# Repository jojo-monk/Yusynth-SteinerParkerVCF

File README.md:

# Yusynth-SteinerParkerVCF
Adaptation du Yusynth [SteinerParkerVCF](http://yusynth.net/Modular/index_en.html) au format Eurorack
Testé et Fonctionnel

J'ai fait une petite erreur sur la sérigraphie du bouton Mode qui se trouvait du mauvais côté du bouton, mais c'est corrigé dans le fichier kicad.
J'ai ajouté un trimmer 100k pour pouvoir régler la résonance.

I made a small mistake on the screen printing of the Mode button which was on the wrong side of the button, but it is corrected in the kicad file.
I added a 100k trimmer to be able to adjust the resonance.

Remplacement de la resistance R19 de 3.9K par un trimpot 100K, (souder la 3eme patte sur la patte centrale)
Replacement of the 3.9K resistor R19 with a 100K trimpot, (solder the 3rd pin on the central pin).

[Build document](https://htmlpreview.github.io/?https://github.com/jojo-monk/Yusynth-SteinerParkerVCF/blob/main/ibom.html)

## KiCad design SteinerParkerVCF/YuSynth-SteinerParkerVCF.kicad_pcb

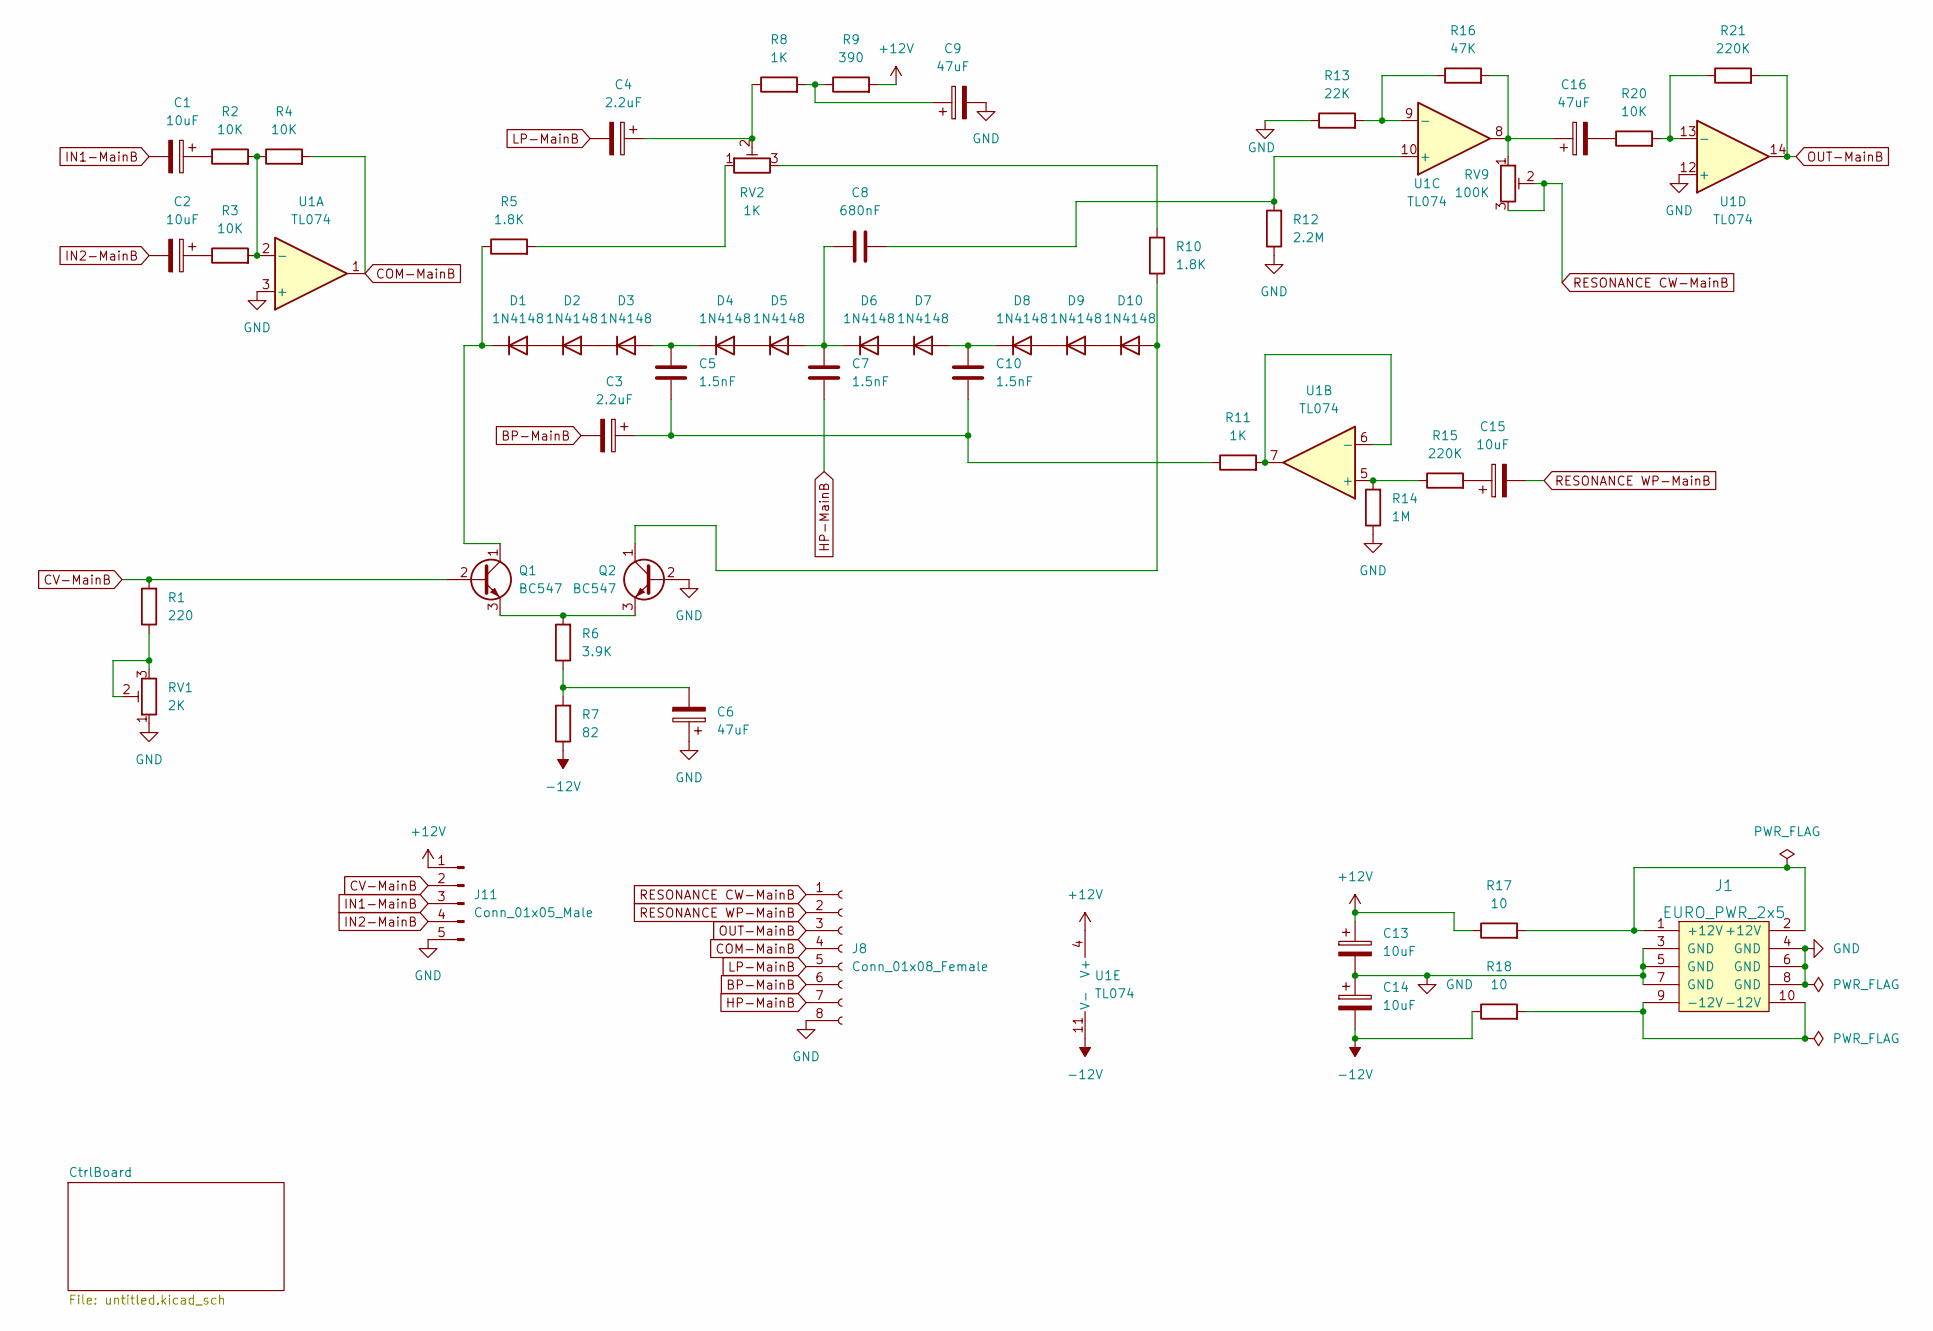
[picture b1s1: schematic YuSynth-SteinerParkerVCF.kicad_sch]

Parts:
C1, C2, C13, C14, C15: 10uF; CP_Radial_D5.0mm_P2.00mm
C3, C4: 2.2uF; CP_Radial_D5.0mm_P2.00mm
C5, C7, C10: 1.5nF; C_Rect_L7.0mm_W3.5mm_P5.00mm
C6, C9, C16: 47uF; CP_Radial_D5.0mm_P2.00mm
C8: 680nF; C_Rect_L7.0mm_W3.5mm_P5.00mm
D1, D2, D3, D4, D5, D6, D7, D8, D9, D10: 1N4148; D_DO-35_SOD27_P7.62mm_Horizontal
J1: EURO_PWR_2x5; Eurorack_power_header
J8: Conn_01x08_Female; PinHeader_1x08_P2.54mm_Vertical
J11: Conn_01x05_Male; PinHeader_1x05_P2.54mm_Vertical
Q1, Q2: BC547; TO-92_HandSolder
R1: 220; R_Axial_DIN0207_L6.3mm_D2.5mm_P5.08mm_Vertical
R2, R3, R4, R20: 10K; R_Axial_DIN0207_L6.3mm_D2.5mm_P5.08mm_Vertical
R5, R10: 1.8K; R_Axial_DIN0207_L6.3mm_D2.5mm_P5.08mm_Vertical
R6: 3.9K; R_Axial_DIN0207_L6.3mm_D2.5mm_P5.08mm_Vertical
R7: 82; R_Axial_DIN0207_L6.3mm_D2.5mm_P5.08mm_Vertical
R8, R11: 1K; R_Axial_DIN0207_L6.3mm_D2.5mm_P5.08mm_Vertical
R9: 390; R_Axial_DIN0207_L6.3mm_D2.5mm_P5.08mm_Vertical
R12: 2.2M; R_Axial_DIN0207_L6.3mm_D2.5mm_P5.08mm_Vertical
R13: 22K; R_Axial_DIN0207_L6.3mm_D2.5mm_P5.08mm_Vertical
R14: 1M; R_Axial_DIN0207_L6.3mm_D2.5mm_P5.08mm_Vertical
R15, R21: 220K; R_Axial_DIN0207_L6.3mm_D2.5mm_P5.08mm_Vertical
R16: 47K; R_Axial_DIN0207_L6.3mm_D2.5mm_P5.08mm_Vertical
R17, R18: 10; R_Axial_DIN0207_L6.3mm_D2.5mm_P5.08mm_Vertical
RV1: 2K; Potentiometer_Bourns_3266Y_Vertical
RV2: 1K; Potentiometer_Bourns_3266Y_Vertical
RV9: 100K; Potentiometer_Bourns_3266Y_Vertical
U1: TL074; DIP-14_W7.62mm_LongPads

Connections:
+12V: C13.1, J11.1, R9.2, R17.1, U1.4 (V+); also elsewhere on the board
-12V: C14.2, R7.1, R18.1, U1.11 (V-)
BP-MainB: C3.2, J8.6
COM-MainB: J8.4, R4.2, U1.1
CV-MainB: J11.2, Q1.2 (B), R1.2
GND: C6.1, C9.2, C13.2, C14.1, J1.3 (GND), J1.4 (GND), J1.5 (GND), J1.6 (GND), J1.7 (GND), J1.8 (GND), J8.8, J11.5, Q2.2 (B), R12.1, R13.1, R14.1, RV1.1, U1.3 (+), U1.12 (+); also elsewhere on the board
HP-MainB: C7.2, J8.7
IN1-MainB: C1.2, J11.3
IN2-MainB: C2.2, J11.4
LP-MainB: C4.2, J8.5
unnamed: C1.1, R2.1
unnamed: C2.1, R3.1
unnamed: C4.1, R8.1, RV2.2
unnamed: C5.1, D3.2 (A), D4.1 (K)
unnamed: C6.2, R6.1, R7.2
unnamed: C7.1, C8.1, D5.2 (A), D6.1 (K)
unnamed: C8.2, R12.2, U1.10 (+)
unnamed: C9.1, R8.2, R9.1
unnamed: C10.1, D7.2 (A), D8.1 (K)
unnamed: C3.1, C5.2, C10.2, R11.1
unnamed: C15.1, R15.2
unnamed: C16.1, R16.2, RV9.1, U1.8
unnamed: C16.2, R20.1
unnamed: D1.1 (K), Q1.1 (C), R5.1
unnamed: D1.2 (A), D2.1 (K)
unnamed: D2.2 (A), D3.1 (K)
unnamed: D4.2 (A), D5.1 (K)
unnamed: D6.2 (A), D7.1 (K)
unnamed: D8.2 (A), D9.1 (K)
unnamed: D9.2 (A), D10.1 (K)
unnamed 37: D10.2 (A), Q2.1 (C), R10.1; also elsewhere on the board
unnamed: J1.1 (+12V), J1.2 (+12V), R17.2
unnamed: J1.9 (-12V), J1.10 (-12V), R18.2
unnamed 46: Q1.3 (E), Q2.3 (E), R6.2; also elsewhere on the board
unnamed: R1.1, RV1.2, RV1.3
unnamed: R2.2, R3.2, R4.1, U1.2 (-)
unnamed: R5.2, RV2.1
unnamed: R10.2, RV2.3
unnamed: R11.2, U1.6 (-), U1.7
unnamed: R13.2, R16.1, U1.9 (-)
unnamed: R14.2, R15.1, U1.5 (+)
unnamed: R20.2, R21.1, U1.13 (-)
OUT-MainB: J8.3, R21.2, U1.14
RESONANCE CW-MainB: J8.1, RV9.2, RV9.3
RESONANCE WP-MainB: C15.2, J8.2

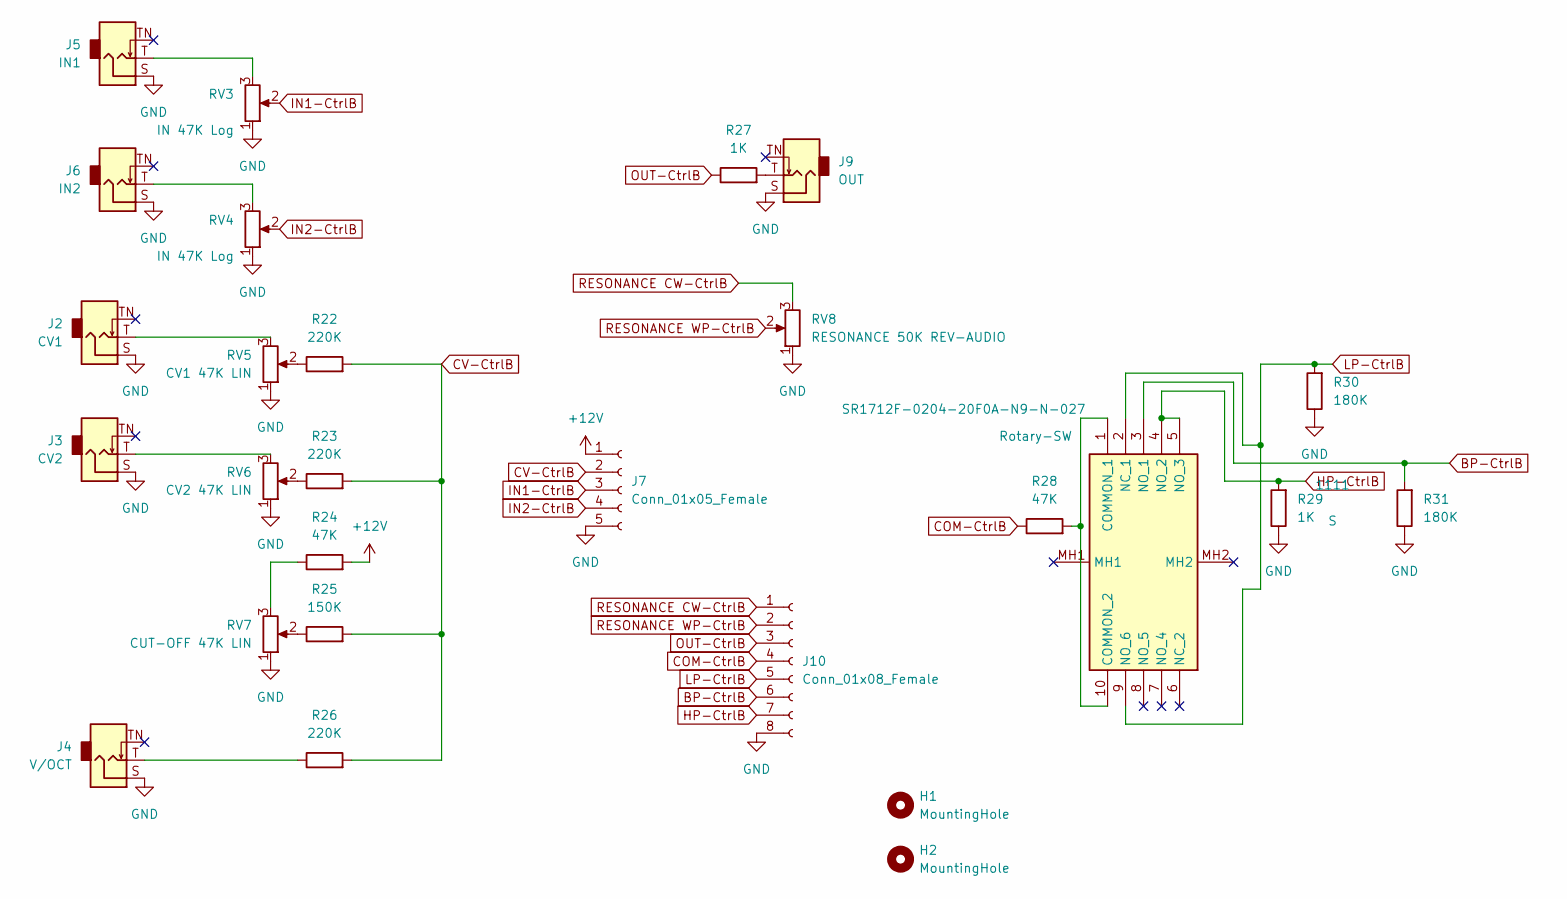
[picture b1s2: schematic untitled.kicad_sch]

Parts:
1111: SR1712F-0204-20F0A-N9-N-027; SR1712F020420F0AN9N027; Mouser Part Number 105-SR1712F-24NS
H1, H2: MountingHole; MountingHole_3.2mm_M3
J2: CV1; Jack_3.5mm_QingPu_WQP-PJ398SM_Vertical
J3: CV2; Jack_3.5mm_QingPu_WQP-PJ398SM_Vertical
J4: V/OCT; Jack_3.5mm_QingPu_WQP-PJ398SM_Vertical
J5: IN1; Jack_3.5mm_QingPu_WQP-PJ398SM_Vertical
J6: IN2; Jack_3.5mm_QingPu_WQP-PJ398SM_Vertical
J7: Conn_01x05_Female; PinHeader_1x05_P2.54mm_Vertical
J9: OUT; Jack_3.5mm_QingPu_WQP-PJ398SM_Vertical
J10: Conn_01x08_Female; PinHeader_1x08_P2.54mm_Vertical
R22, R23, R26: 220K; R_Axial_DIN0207_L6.3mm_D2.5mm_P5.08mm_Vertical
R24, R28: 47K; R_Axial_DIN0207_L6.3mm_D2.5mm_P5.08mm_Vertical
R25: 150K; R_Axial_DIN0207_L6.3mm_D2.5mm_P5.08mm_Vertical
R27, R29: 1K; R_Axial_DIN0207_L6.3mm_D2.5mm_P5.08mm_Vertical
R30, R31: 180K; R_Axial_DIN0207_L6.3mm_D2.5mm_P5.08mm_Vertical
RV3, RV4: IN 47K Log; Potentiometer_Alpha_RD901F-40-00D_Single_Vertical
RV5: CV1 47K LIN; Potentiometer_Alpha_RD901F-40-00D_Single_Vertical
RV6: CV2 47K LIN; Potentiometer_Alpha_RD901F-40-00D_Single_Vertical
RV7: CUT-OFF 47K LIN; Potentiometer_Alpha_RD901F-40-00D_Single_Vertical
RV8: RESONANCE 50K REV-AUDIO; Potentiometer_Alpha_RD901F-40-00D_Single_Vertical

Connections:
+12V: J7.1, R24.2; also elsewhere on the board
BP-CtrlB: 1111.3 (NO_1), J10.6, R31.2
COM-CtrlB: J10.4, R28.1
CV-CtrlB: J7.2, R22.2, R23.2, R25.2, R26.2
GND: J2.S, J3.S, J4.S, J5.S, J6.S, J7.5, J9.S, J10.8, R29.1, R30.1, R31.1, RV3.1, RV4.1, RV5.1, RV6.1, RV7.1, RV8.1; also elsewhere on the board
HP-CtrlB: 1111.4 (NO_2), 1111.5 (NO_3), J10.7, R29.2
IN1-CtrlB: J7.3, RV3.2
IN2-CtrlB: J7.4, RV4.2
LP-CtrlB: 1111.2 (NC_1), 1111.9 (NO_6), J10.5, R30.2
unnamed: J2.T, RV5.3
unnamed: J3.T, RV6.3
unnamed: J4.T, R26.1
unnamed: J5.T, RV3.3
unnamed: J6.T, RV4.3
unnamed: J9.T, R27.2
unnamed: R22.1, RV5.2
unnamed: R23.1, RV6.2
unnamed: R24.1, RV7.3
unnamed: R25.1, RV7.2
unnamed: 1111.1 (COMMON_1), 1111.10 (COMMON_2), R28.2
OUT-CtrlB: J10.3, R27.1
RESONANCE CW-CtrlB: J10.1, RV8.3
RESONANCE WP-CtrlB: J10.2, RV8.2

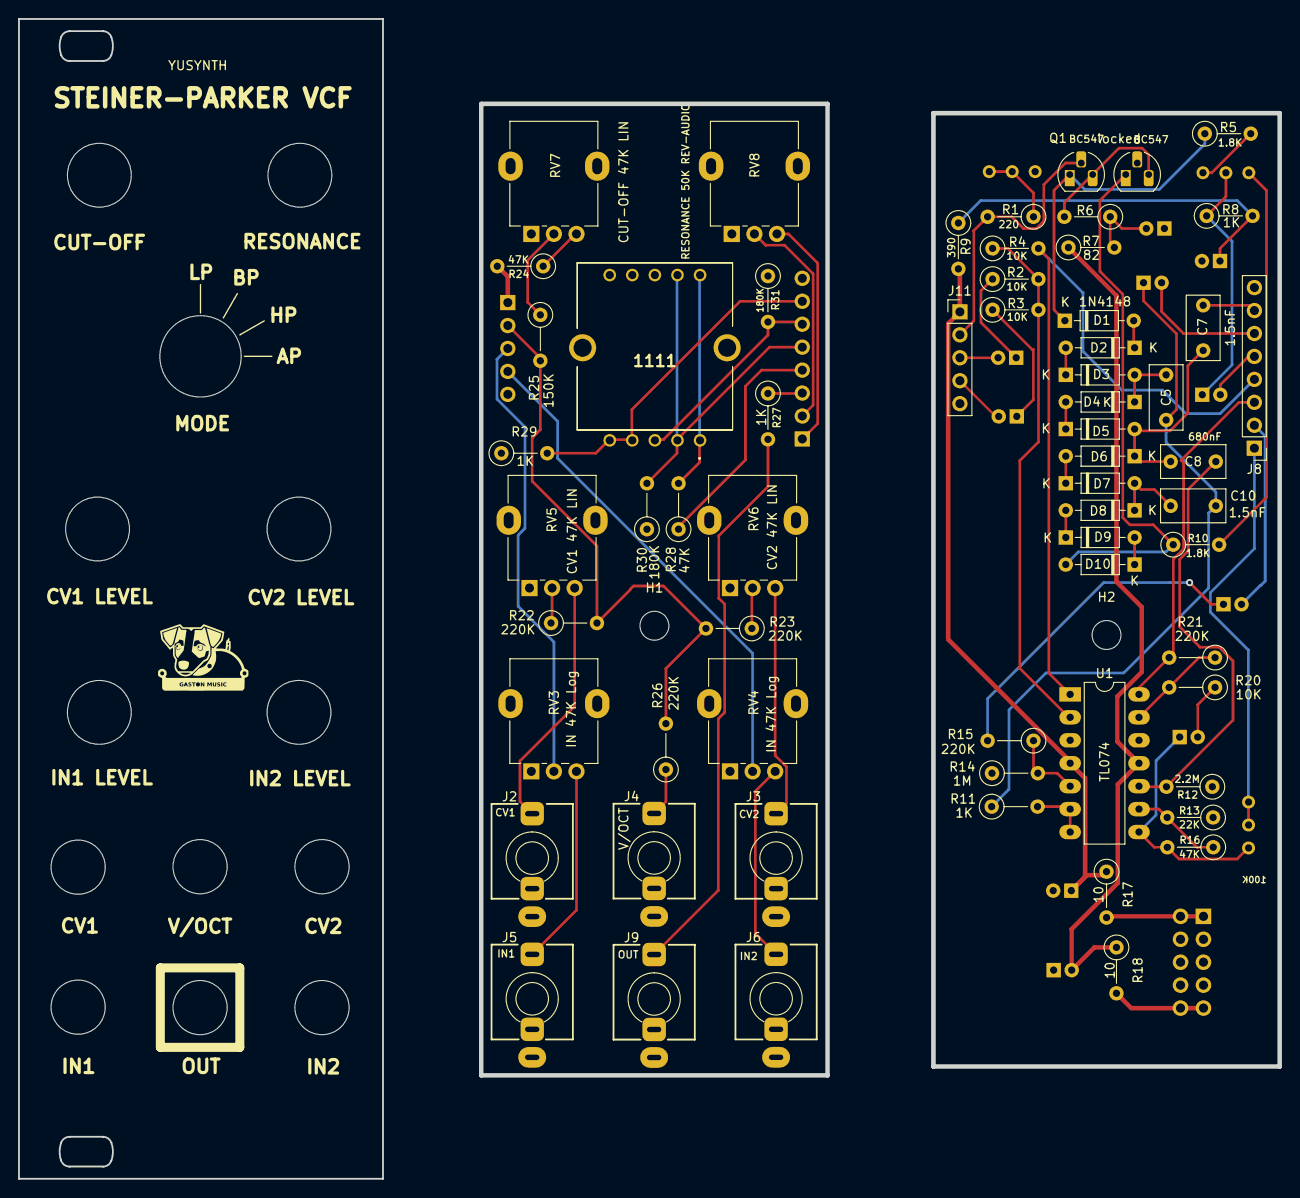
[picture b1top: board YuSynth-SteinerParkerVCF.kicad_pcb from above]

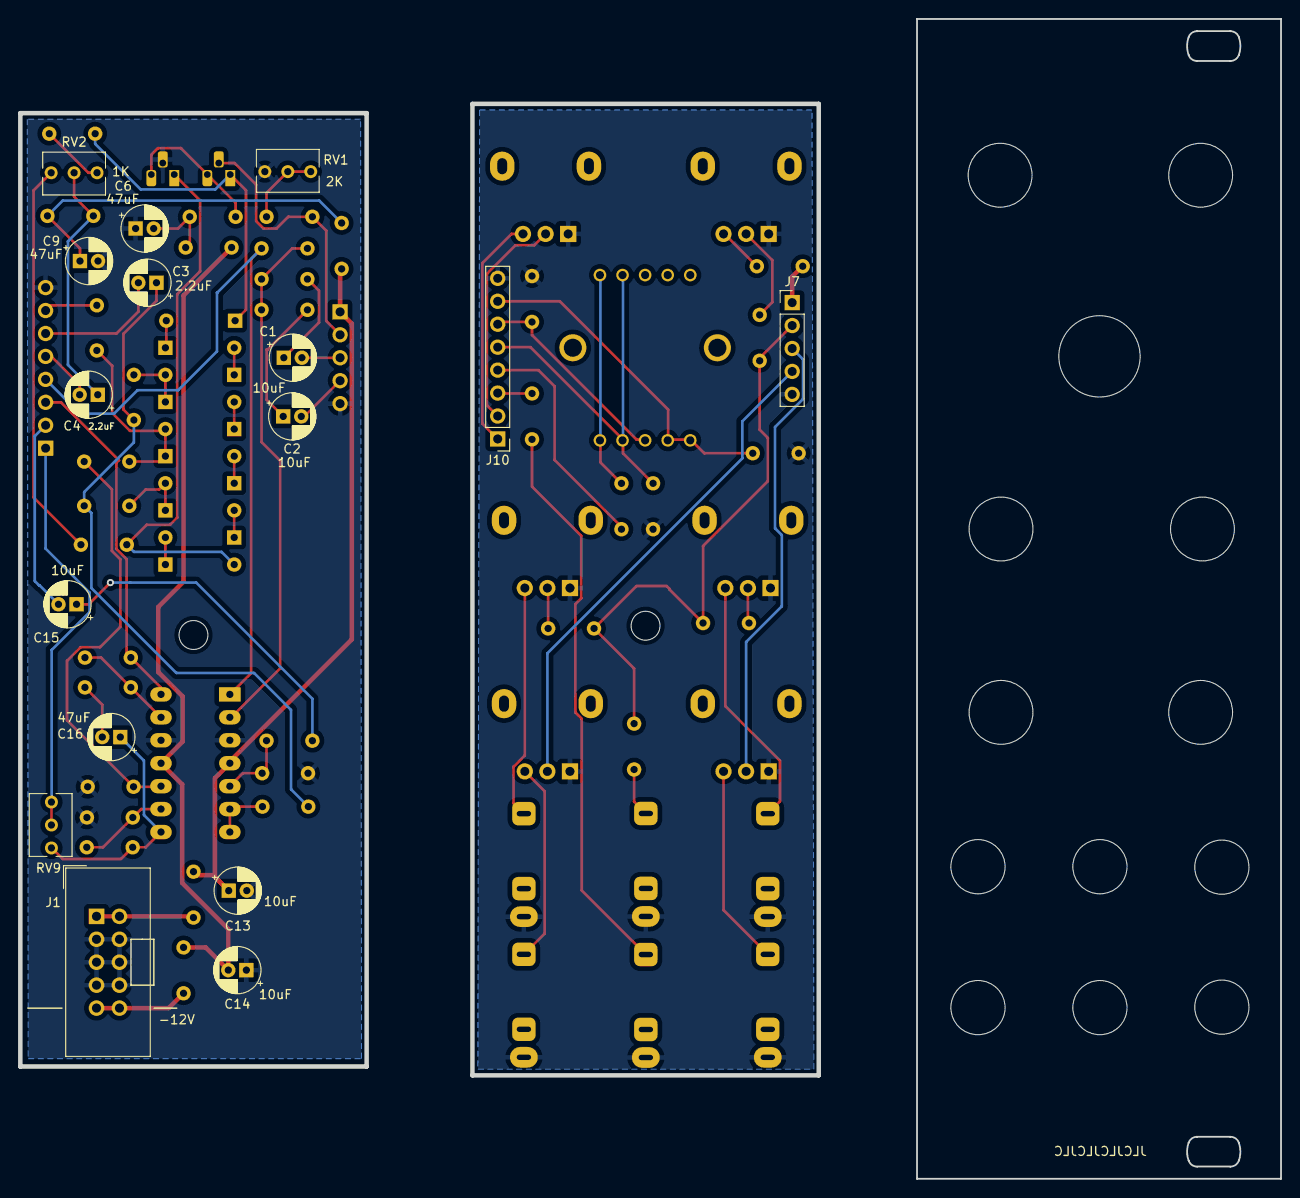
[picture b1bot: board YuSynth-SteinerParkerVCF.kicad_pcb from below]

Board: 2 copper layers, 139.4 x 128.1 mm, 80 parts (16 on the bottom side), 66 nets.

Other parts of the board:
locked: BC547; TO-92_HandSolder

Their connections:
GND: locked.2 (B); also elsewhere on the board
unnamed 37: locked.1 (C); also elsewhere on the board
unnamed 46: locked.3 (E); also elsewhere on the board

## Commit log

2023-08-12 init
2023-08-31 correction FrontPanel
2023-09-13 add photos
2023-09-13 modif pcb
2023-09-13 correction ibom
2023-10-20 add pdf
